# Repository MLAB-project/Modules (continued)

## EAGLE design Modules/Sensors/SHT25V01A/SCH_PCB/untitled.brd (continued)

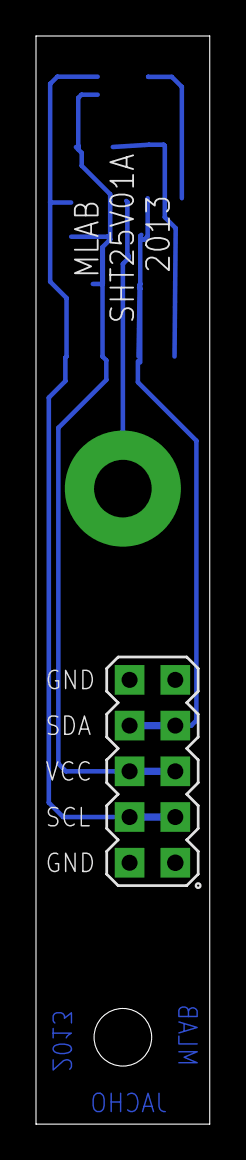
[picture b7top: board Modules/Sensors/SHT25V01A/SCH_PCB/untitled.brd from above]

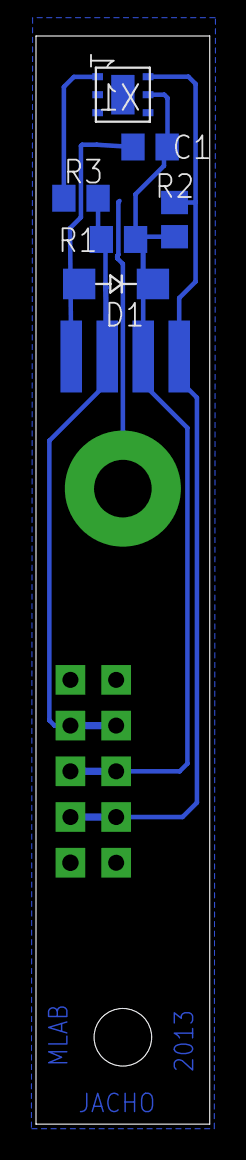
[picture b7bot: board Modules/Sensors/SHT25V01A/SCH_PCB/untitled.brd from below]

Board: 2 copper layers, 9.7 x 60.5 mm, 9 parts (7 on the bottom side), 5 nets.
